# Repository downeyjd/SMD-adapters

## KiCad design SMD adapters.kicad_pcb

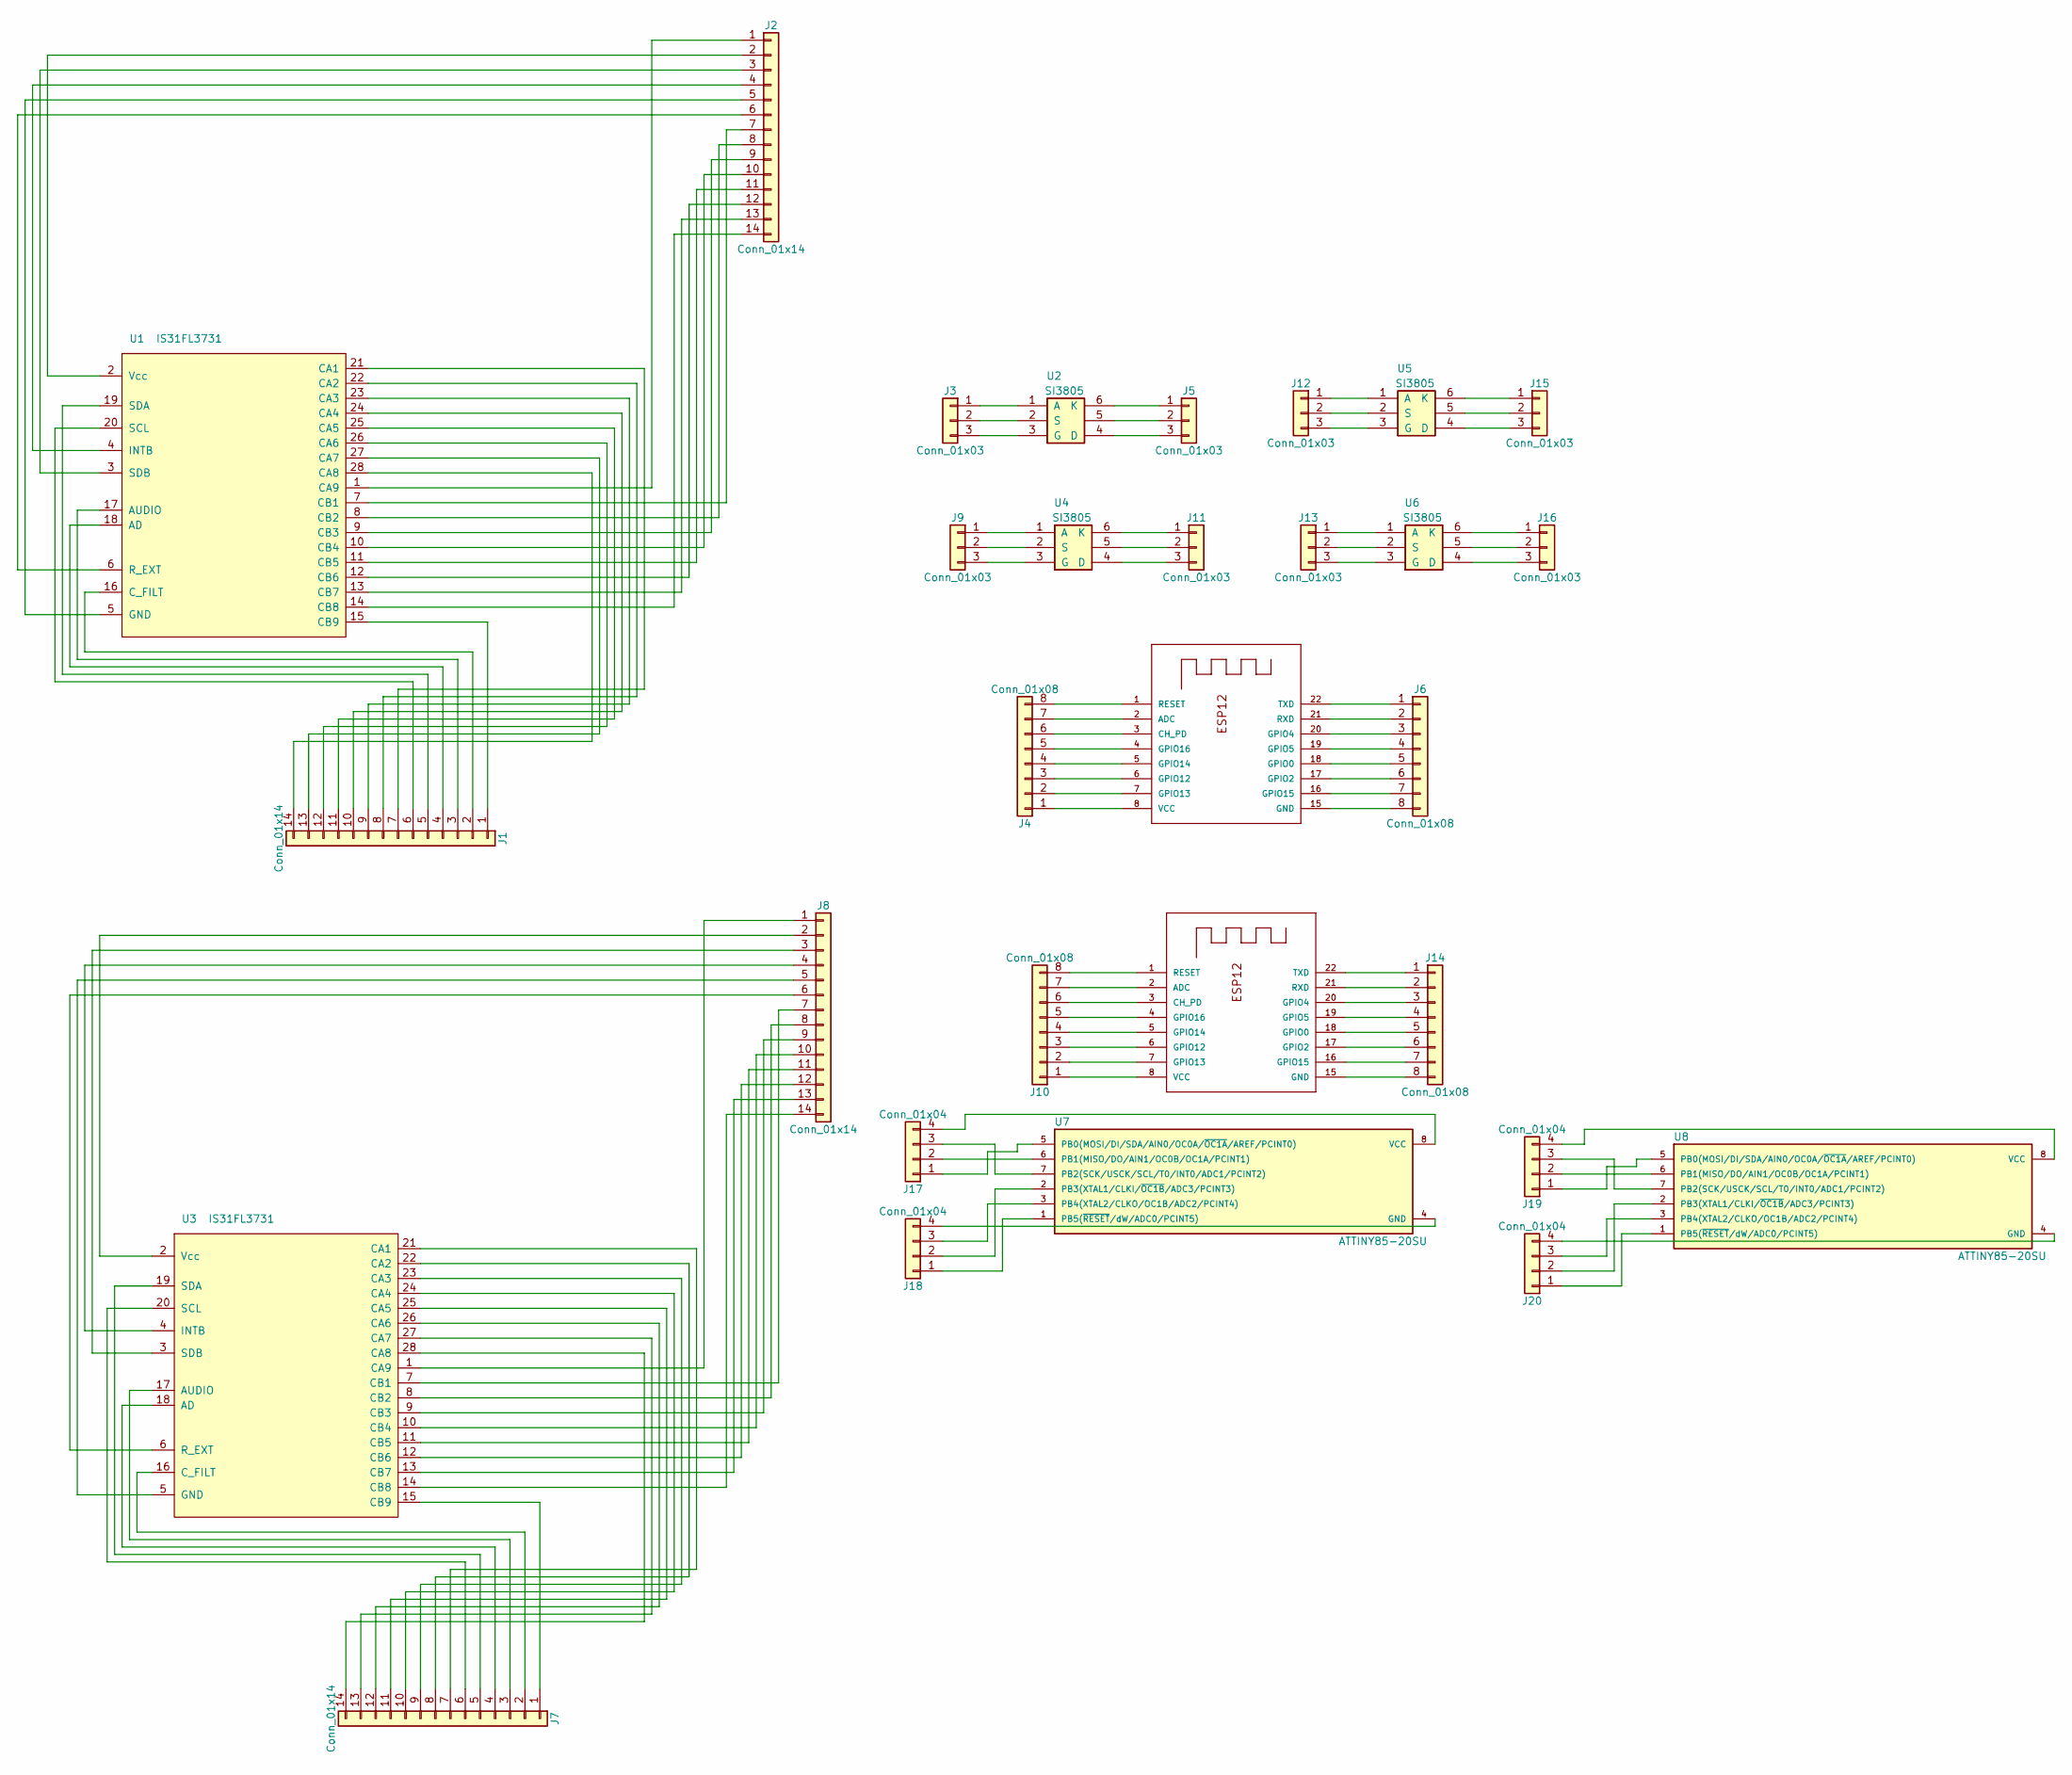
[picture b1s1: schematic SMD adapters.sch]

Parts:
J1, J2, J7, J8: Conn_01x14; Pin_Header_Straight_1x14_Pitch2.54mm
J3, J5, J9, J11, J12, J13, J15, J16: Conn_01x03; Pin_Header_Straight_1x03_Pitch2.54mm
J4, J6, J10, J14: Conn_01x08; Pin_Header_Straight_1x08_Pitch2.54mm
J17, J18, J19, J20: Conn_01x04; Pin_Header_Straight_1x04_Pitch2.54mm
U1, U3: IS31FL3731; QFN-28-1EP_4x4mm_Pitch0.4mm
U2, U4, U5, U6: SI3805; TSOP-6_1.65x3.05mm_Pitch0.95mm
U7, U8: ATTINY85-20SU; SOT-23-8_Handsoldering
X1, X2: ESP-12; ESP-12E

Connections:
unnamed 0: J1.1, U1.15 (CB9); also elsewhere on the board
unnamed 1: J1.2, U1.16 (C_FILT); also elsewhere on the board
unnamed 2: J1.3, U1.17 (AUDIO); also elsewhere on the board
unnamed 3: J1.4, U1.18 (AD); also elsewhere on the board
unnamed 4: J1.5, U1.19 (SDA); also elsewhere on the board
unnamed 5: J1.6, U1.20 (SCL); also elsewhere on the board
unnamed 6: J1.7, U1.21 (CA1); also elsewhere on the board
unnamed 7: J1.8, U1.22 (CA2); also elsewhere on the board
unnamed 8: J1.9, U1.23 (CA3); also elsewhere on the board
unnamed 9: J1.10, U1.24 (CA4); also elsewhere on the board
unnamed 10: J1.11, U1.25 (CA5); also elsewhere on the board
unnamed 11: J1.12, U1.26 (CA6); also elsewhere on the board
unnamed 12: J1.13, U1.27 (CA7); also elsewhere on the board
unnamed 13: J1.14, U1.28 (CA8); also elsewhere on the board
unnamed 14: J2.1, U1.1 (CA9); also elsewhere on the board
unnamed 15: J2.2, U1.2 (Vcc); also elsewhere on the board
unnamed 16: J2.3, U1.3 (SDB); also elsewhere on the board
unnamed 17: J2.4, U1.4 (INTB); also elsewhere on the board
unnamed 18: J2.5, U1.5 (GND); also elsewhere on the board
unnamed 19: J2.6, U1.6 (R_EXT); also elsewhere on the board
unnamed 20: J2.7, U1.7 (CB1); also elsewhere on the board
unnamed 21: J2.8, U1.8 (CB2); also elsewhere on the board
unnamed 22: J2.9, U1.9 (CB3); also elsewhere on the board
unnamed 23: J2.10, U1.10 (CB4); also elsewhere on the board
unnamed 24: J2.11, U1.11 (CB5); also elsewhere on the board
unnamed 25: J2.12, U1.12 (CB6); also elsewhere on the board
unnamed 26: J2.13, U1.13 (CB7); also elsewhere on the board
unnamed 27: J2.14, U1.14 (CB8); also elsewhere on the board
unnamed: J3.1, U2.1 (A)
unnamed: J3.2, U2.2 (S)
unnamed: J3.3, U2.3 (G)
unnamed: J4.1, X1.8 (VCC)
unnamed: J4.2, X1.7 (GPIO13)
unnamed: J4.3, X1.6 (GPIO12)
unnamed: J4.4, X1.5 (GPIO14)
unnamed: J4.5, X1.4 (GPIO16)
unnamed: J4.6, X1.3 (CH_PD)
unnamed: J4.7, X1.2 (ADC)
unnamed: J4.8, X1.1 (RESET)
unnamed: J5.1, U2.6 (K)
unnamed: J5.2, U2.5
unnamed: J5.3, U2.4 (D)
unnamed: J6.1, X1.22 (TXD)
unnamed: J6.2, X1.21 (RXD)
unnamed: J6.3, X1.20 (GPIO4)
unnamed: J6.4, X1.19 (GPIO5)
unnamed: J6.5, X1.18 (GPIO0)
unnamed: J6.6, X1.17 (GPIO2)
unnamed: J6.7, X1.16 (GPIO15)
unnamed: J6.8, X1.15 (GND)
unnamed: J7.1, U3.15 (CB9)
unnamed: J7.2, U3.16 (C_FILT)
unnamed: J7.3, U3.17 (AUDIO)
unnamed: J7.4, U3.18 (AD)
unnamed: J7.5, U3.19 (SDA)
unnamed: J7.6, U3.20 (SCL)
unnamed: J7.7, U3.21 (CA1)
unnamed: J7.8, U3.22 (CA2)
unnamed: J7.9, U3.23 (CA3)
unnamed: J7.10, U3.24 (CA4)
unnamed: J7.11, U3.25 (CA5)
unnamed: J7.12, U3.26 (CA6)
unnamed: J7.13, U3.27 (CA7)
unnamed: J7.14, U3.28 (CA8)
unnamed: J8.1, U3.1 (CA9)
unnamed: J8.2, U3.2 (Vcc)
unnamed: J8.3, U3.3 (SDB)
unnamed: J8.4, U3.4 (INTB)
unnamed: J8.5, U3.5 (GND)
unnamed: J8.6, U3.6 (R_EXT)
unnamed: J8.7, U3.7 (CB1)
unnamed: J8.8, U3.8 (CB2)
unnamed: J8.9, U3.9 (CB3)
unnamed: J8.10, U3.10 (CB4)
unnamed: J8.11, U3.11 (CB5)
unnamed: J8.12, U3.12 (CB6)
unnamed: J8.13, U3.13 (CB7)
unnamed: J8.14, U3.14 (CB8)
unnamed: J9.1, U4.1 (A)
unnamed: J9.2, U4.2 (S)
unnamed: J9.3, U4.3 (G)
unnamed: J10.1, X2.8 (VCC)
unnamed: J10.2, X2.7 (GPIO13)
unnamed: J10.3, X2.6 (GPIO12)
unnamed: J10.4, X2.5 (GPIO14)
unnamed: J10.5, X2.4 (GPIO16)
unnamed: J10.6, X2.3 (CH_PD)
unnamed: J10.7, X2.2 (ADC)
unnamed: J10.8, X2.1 (RESET)
unnamed: J11.1, U4.6 (K)
unnamed: J11.2, U4.5
unnamed: J11.3, U4.4 (D)
unnamed: J12.1, U5.1 (A)
unnamed: J12.2, U5.2 (S)
unnamed: J12.3, U5.3 (G)
unnamed: J13.1, U6.1 (A)
unnamed: J13.2, U6.2 (S)
unnamed: J13.3, U6.3 (G)
unnamed: J14.1, X2.22 (TXD)
unnamed: J14.2, X2.21 (RXD)
unnamed: J14.3, X2.20 (GPIO4)
unnamed: J14.4, X2.19 (GPIO5)
unnamed: J14.5, X2.18 (GPIO0)
unnamed: J14.6, X2.17 (GPIO2)
unnamed: J14.7, X2.16 (GPIO15)
unnamed: J14.8, X2.15 (GND)
unnamed: J15.1, U5.6 (K)
unnamed: J15.2, U5.5
unnamed: J15.3, U5.4 (D)
unnamed: J16.1, U6.6 (K)
unnamed: J16.2, U6.5
unnamed: J16.3, U6.4 (D)
unnamed: J17.1, U7.5 (PB0(MOSI/DI/SDA/AIN0/OC0A/~OC1A~/AREF/P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)
unnamed: J17.2, U7.6 (PB1(MISO/DO/AIN1/OC0B/OC1A/PCINT1))
unnamed: J17.3, U7.7 (PB2(SCK/USCK/SCL/T0/INT0/ADC1/PCINT2))
unnamed: J17.4, U7.8 (VCC)
unnamed: J18.1, U7.1 (PB5(~RESET~/dW/ADC0/PCINT5))
unnamed: J18.2, U7.2 (PB3(XTAL1/CLKI/~OC1B~/ADC3/PCINT3))
unnamed: J18.3, U7.3 (PB4(XTAL2/CLKO/OC1B/ADC2/PCINT4))
unnamed: J18.4, U7.4 (GND)
unnamed: J19.1, U8.5 (PB0(MOSI/DI/SDA/AIN0/OC0A/~OC1A~/AREF/P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)
unnamed: J19.2, U8.6 (PB1(MISO/DO/AIN1/OC0B/OC1A/PCINT1))
unnamed: J19.3, U8.7 (PB2(SCK/USCK/SCL/T0/INT0/ADC1/PCINT2))
unnamed: J19.4, U8.8 (VCC)
unnamed: J20.1, U8.1 (PB5(~RESET~/dW/ADC0/PCINT5))
unnamed: J20.2, U8.2 (PB3(XTAL1/CLKI/~OC1B~/ADC3/PCINT3))
unnamed: J20.3, U8.3 (PB4(XTAL2/CLKO/OC1B/ADC2/PCINT4))
unnamed: J20.4, U8.4 (GND)

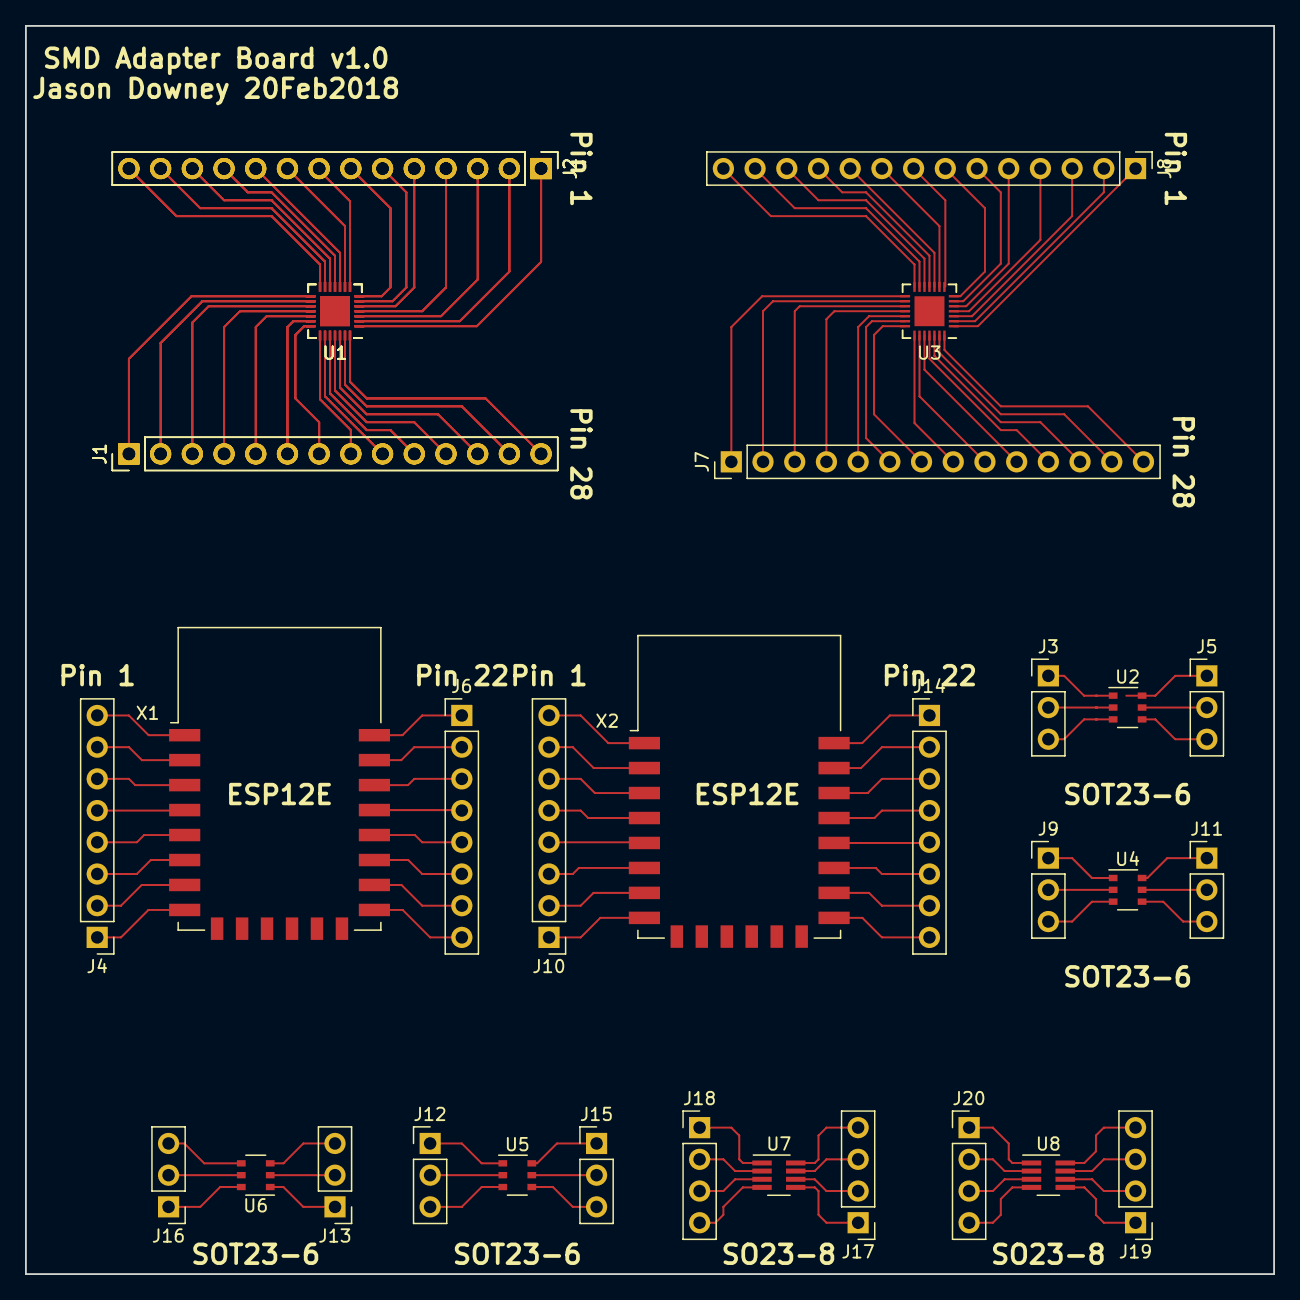
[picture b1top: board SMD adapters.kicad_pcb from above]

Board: 2 copper layers, 100.0 x 100.0 mm, 33 parts (0 on the bottom side), 128 nets.

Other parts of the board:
J1#2, J2#2: Conn_01x14; Pin_Header_Straight_1x14_Pitch2.54mm
U1#2: IS31FL3731; QFN-28-1EP_4x4mm_Pitch0.4mm

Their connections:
unnamed 0: J1#2.1, U1#2.15; also elsewhere on the board
unnamed 1: J1#2.2, U1#2.16; also elsewhere on the board
unnamed 2: J1#2.3, U1#2.17; also elsewhere on the board
unnamed 3: J1#2.4, U1#2.18; also elsewhere on the board
unnamed 4: J1#2.5, U1#2.19; also elsewhere on the board
unnamed 5: J1#2.6, U1#2.20; also elsewhere on the board
unnamed 6: J1#2.7, U1#2.21; also elsewhere on the board
unnamed 7: J1#2.8, U1#2.22; also elsewhere on the board
unnamed 8: J1#2.9, U1#2.23; also elsewhere on the board
unnamed 9: J1#2.10, U1#2.24; also elsewhere on the board
unnamed 10: J1#2.11, U1#2.25; also elsewhere on the board
unnamed 11: J1#2.12, U1#2.26; also elsewhere on the board
unnamed 12: J1#2.13, U1#2.27; also elsewhere on the board
unnamed 13: J1#2.14, U1#2.28; also elsewhere on the board
unnamed 14: J2#2.1, U1#2.1; also elsewhere on the board
unnamed 15: J2#2.2, U1#2.2; also elsewhere on the board
unnamed 16: J2#2.3, U1#2.3; also elsewhere on the board
unnamed 17: J2#2.4, U1#2.4; also elsewhere on the board
unnamed 18: J2#2.5, U1#2.5; also elsewhere on the board
unnamed 19: J2#2.6, U1#2.6; also elsewhere on the board
unnamed 20: J2#2.7, U1#2.7; also elsewhere on the board
unnamed 21: J2#2.8, U1#2.8; also elsewhere on the board
unnamed 22: J2#2.9, U1#2.9; also elsewhere on the board
unnamed 23: J2#2.10, U1#2.10; also elsewhere on the board
unnamed 24: J2#2.11, U1#2.11; also elsewhere on the board
unnamed 25: J2#2.12, U1#2.12; also elsewhere on the board
unnamed 26: J2#2.13, U1#2.13; also elsewhere on the board
unnamed 27: J2#2.14, U1#2.14; also elsewhere on the board
